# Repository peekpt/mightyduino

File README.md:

## Mightyduino
A DIY Arduino type hardware board based on ATmega644p Atmega1284p

This project is free and based on @MCUDude's [MightyCore](https://github.com/MCUdude/MightyCore) which has awesome well designed kits for serious development with AVR's.

Mightyduino is an Arduino with more memory than an Arduino Pro mini. It can use 644p (64k) or 1284p (128k) chips. Its voltage can be configured by U1 and the frequecy can be configured by the Murata's ressonator (crystal).
It has a power led and another one connected to pin D0. The push button performs reset. DTR pin can be used to external reset. The RAW pin is the input voltage **<16v**. The VCC pin is the regulator output and IC voltage, it can be loaded up to peak of **500mA**.

To burn the **bootloader** (optiboot 6.0) you must first install the [MightyCore boards](https://github.com/MCUdude/MightyCore#how-to-install) on Arduino App  , connect the ICSP pins to your bootloader programming hardware (eg. USBASP), select one of MCUDude's board that meet the specs you use and burn bootloader.
Then you can access (ttl-serial dongle) like a normal arduino on the serial pins (like arduino pro mini). Mightyduino uses the 'standard' pin mapping.

###Version History
- v1.3 - Changed C1 C3 footprint, add reset pin for SPI programming.
- v1.2 - Switch U1 shutdown pin 3 voltage to RAW
- v1.1 - Switched Led from pin D13 to D0, cosmetic improvements
- v1.0 - Initial release

###Quick Links:

Order boards from [OSHPark]
(https://oshpark.com/shared_projects/zuZ4OIae)

Or download the [Gerber files](https://github.com/peekpt/mightyduino/raw/master/gerber/gerbers.zip) for other pcb maker

Download the schematic [PDF](https://github.com/peekpt/mightyduino/blob/master/schematic.pdf)

ATmega datasheet [644p](http://www.atmel.com/images/doc2593.pdf) [1284p](http://www.atmel.com/images/doc8059.pdf)

## Screenshots

###Components

### Top

### Bottom

###Pin Mapping

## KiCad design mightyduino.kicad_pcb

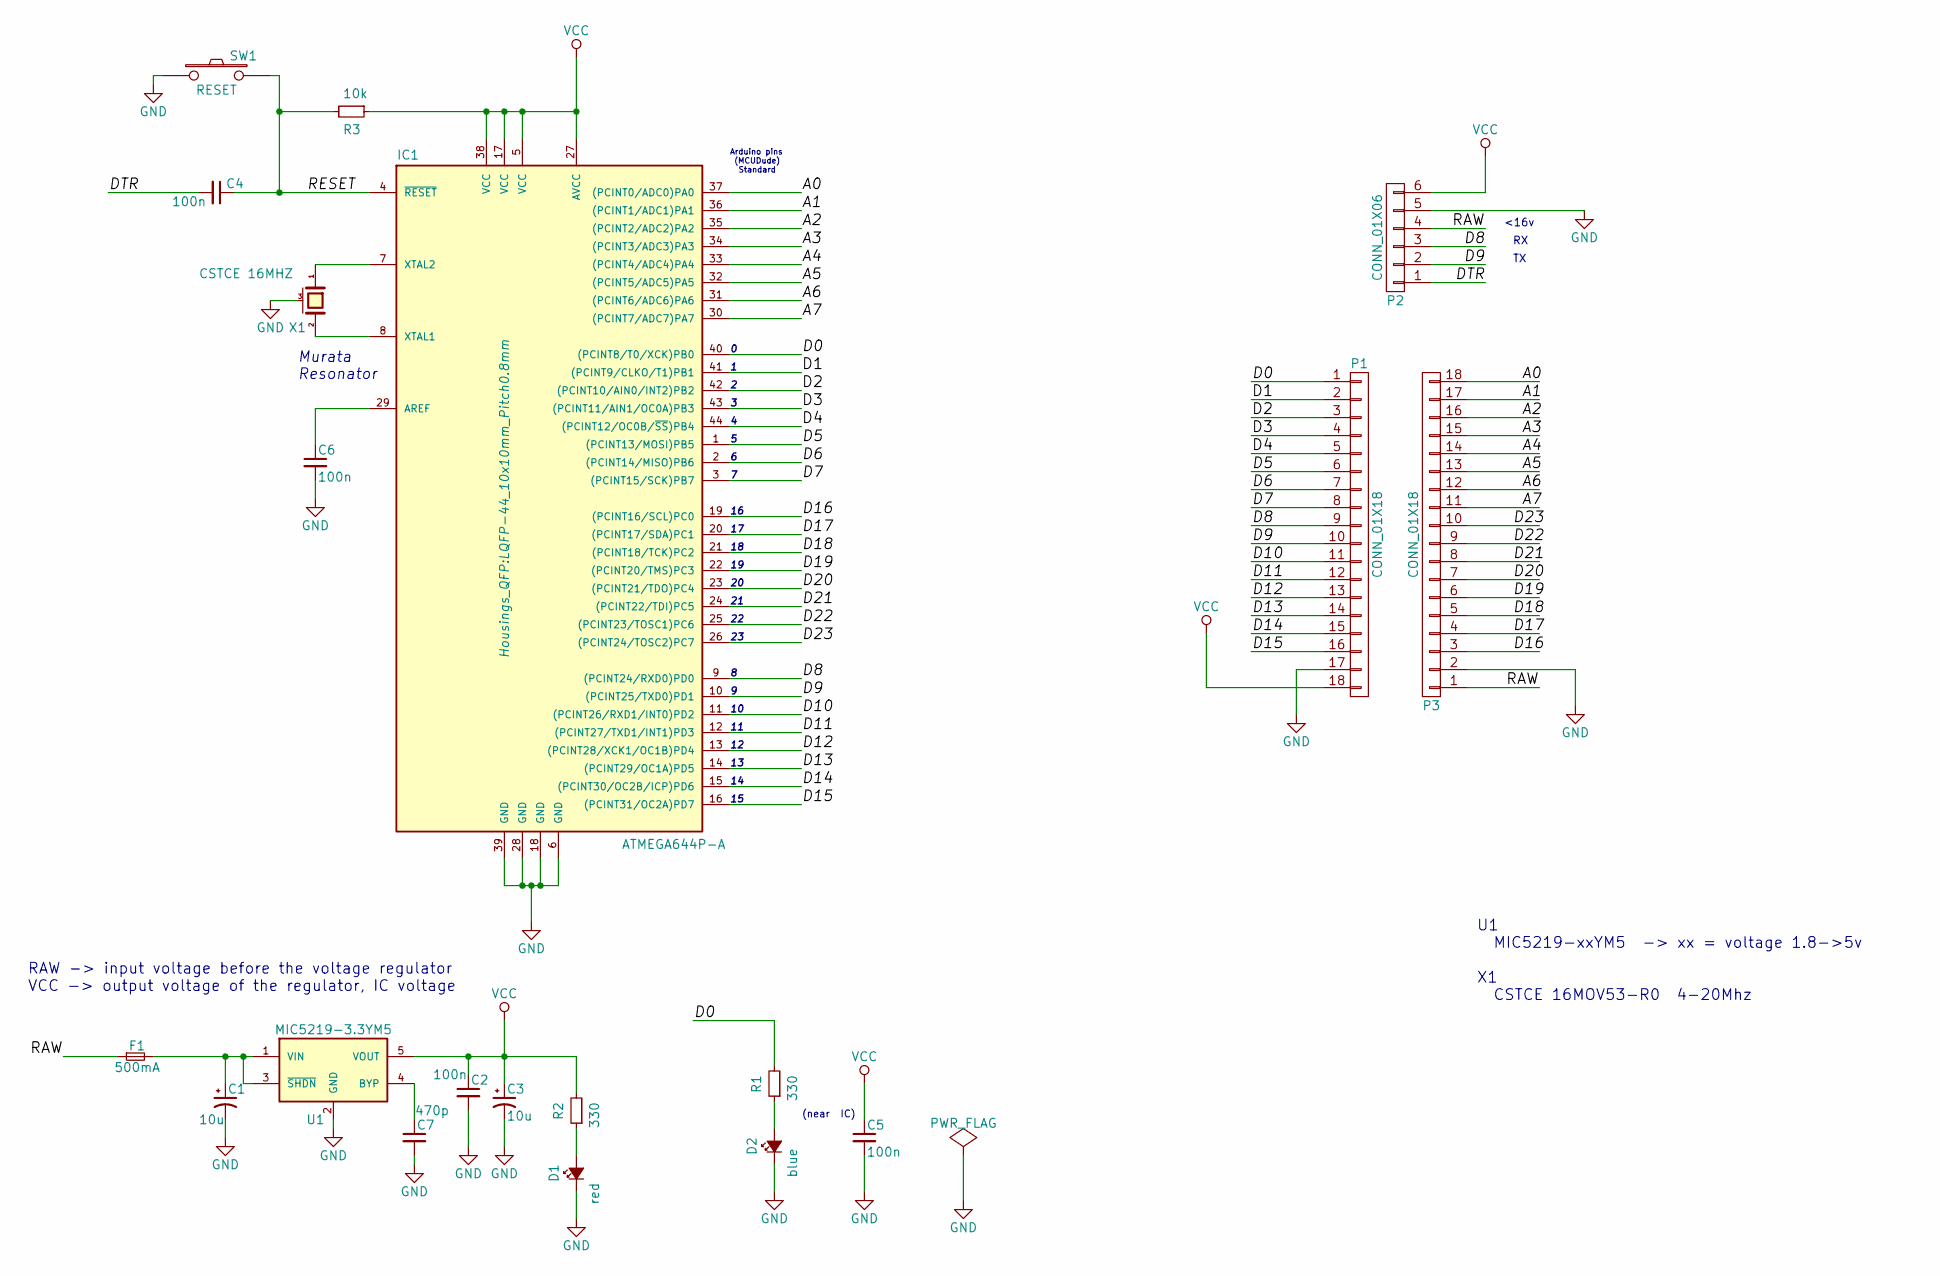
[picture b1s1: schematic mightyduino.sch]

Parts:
C1, C3: 10u; C_0805
C2, C4, C5, C6: 100n; C_0805
C7: 470p; C_0805
D1: red; LED_0805
D2: blue; LED_0805
F1: 500mA; C_0805_HandSoldering
IC1: ATMEGA644P-A; LQFP-44_10x10mm_Pitch0.8mm
P1, P3: CONN_01X18; Pin_Header_Straight_1x18
P2: CONN_01X06; Pin_Header_Straight_1x06
R1, R2: 330; R_0805
R3: 10k; R_0805
SW1: RESET; SW_SPST_TL3342
U1: MIC5219-3.3YM5; SOT-23-5
X1: CSTCE 16MHZ; CSTCEv2

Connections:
/A0: IC1.37 ((PCINT0/ADC0)PA0), P3.18
/A1: IC1.36 ((PCINT1/ADC1)PA1), P3.17
/A2: IC1.35 ((PCINT2/ADC2)PA2), P3.16
/A3: IC1.34 ((PCINT3/ADC3)PA3), P3.15
/A4: IC1.33 ((PCINT4/ADC4)PA4), P3.14
/A5: IC1.32 ((PCINT5/ADC5)PA5), P3.13
/A6: IC1.31 ((PCINT6/ADC6)PA6), P3.12
/A7: IC1.30 ((PCINT7/ADC7)PA7), P3.11
/D0: IC1.40 ((PCINT8/T0/XCK)PB0), P1.1, R1.2
/D1: IC1.41 ((PCINT9/CLKO/T1)PB1), P1.2
/D2: IC1.42 ((PCINT10/AIN0/INT2)PB2), P1.3
/D3: IC1.43 ((PCINT11/AIN1/OC0A)PB3), P1.4
/D4: IC1.44 ((PCINT12/OC0B/~SS~)PB4), P1.5
/D5: IC1.1 ((PCINT13/MOSI)PB5), P1.6
/D6: IC1.2 ((PCINT14/MISO)PB6), P1.7
/D7: IC1.3 ((PCINT15/SCK)PB7), P1.8
/D8: IC1.9 ((PCINT24/RXD0)PD0), P1.9, P2.3
/D9: IC1.10 ((PCINT25/TXD0)PD1), P1.10, P2.2
/D10: IC1.11 ((PCINT26/RXD1/INT0)PD2), P1.11
/D11: IC1.12 ((PCINT27/TXD1/INT1)PD3), P1.12
/D12: IC1.13 ((PCINT28/XCK1/OC1B)PD4), P1.13
/D13: IC1.14 ((PCINT29/OC1A)PD5), P1.14
/D14: IC1.15 ((PCINT30/OC2B/ICP)PD6), P1.15
/D15: IC1.16 ((PCINT31/OC2A)PD7), P1.16
/D16: IC1.19 ((PCINT16/SCL)PC0), P3.3
/D17: IC1.20 ((PCINT17/SDA)PC1), P3.4
/D18: IC1.21 ((PCINT18/TCK)PC2), P3.5
/D19: IC1.22 ((PCINT20/TMS)PC3), P3.6
/D20: IC1.23 ((PCINT21/TDO)PC4), P3.7
/D21: IC1.24 ((PCINT22/TDI)PC5), P3.8
/D22: IC1.25 ((PCINT23/TOSC1)PC6), P3.9
/D23: IC1.26 ((PCINT24/TOSC2)PC7), P3.10
/DTR: C4.2, P2.1
/RAW: F1.1, P2.4, P3.1
/RESET: C4.1, IC1.4 (~RESET), R3.2, SW1.2
GND: C1.2, C2.2, C3.2, C5.2, C6.2, C7.2, D1.1 (K), D2.1 (K), IC1.6 (GND), IC1.18 (GND), IC1.28 (GND), IC1.39 (GND), P1.17, P2.5, P3.2, SW1.1, U1.2 (GND), X1.3 (case)
unnamed: C1.1, F1.2, U1.1 (VIN), U1.3 (~SHDN~)
unnamed: C6.1, IC1.29 (AREF)
unnamed: C7.1, U1.4 (BYP)
unnamed: D1.2 (A), R2.1
unnamed: D2.2 (A), R1.1
unnamed: IC1.7 (XTAL2), X1.1
unnamed: IC1.8 (XTAL1), X1.2
VCC: C2.1, C3.1, C5.1, IC1.5 (VCC), IC1.17 (VCC), IC1.27 (AVCC), IC1.38 (VCC), P1.18, P2.6, R2.2, R3.1, U1.5 (VOUT)

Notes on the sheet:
Murata Resonator
Arduino pins (MCUDude) Standard
(near IC)
<16v
U1 MIC5219-xxYM5 -> xx = voltage 1.8->5v X1 CSTCE 16MOV53-R0 4-20Mhz
RAW -> input voltage before the voltage regulator VCC -> output voltage of the regulator, IC voltage

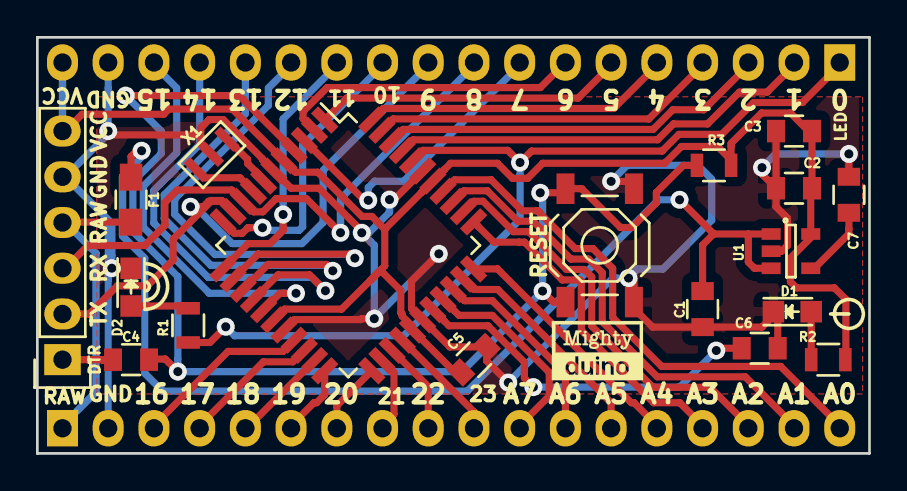
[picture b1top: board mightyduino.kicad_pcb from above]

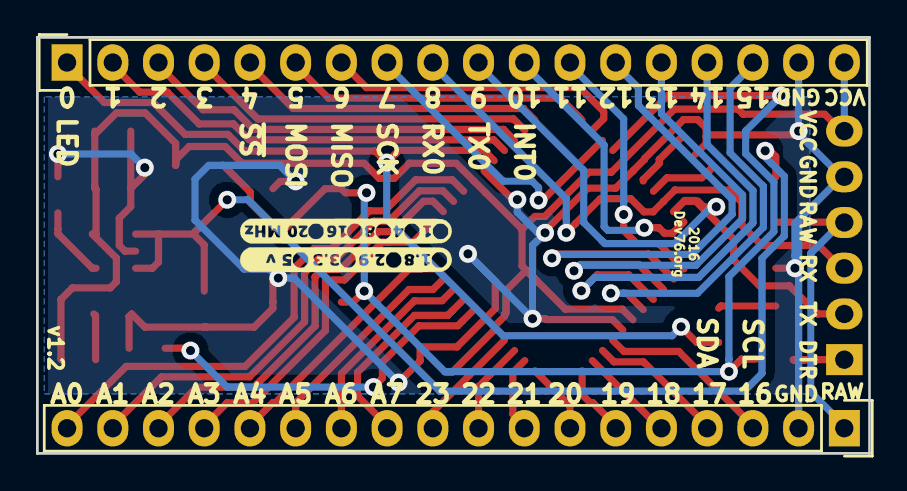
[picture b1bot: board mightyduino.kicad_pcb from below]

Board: 2 copper layers, 46.2 x 23.1 mm, 20 parts (2 on the bottom side), 44 nets.

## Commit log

2016-12-05 Public release 1.0
2016-12-05 add imgs
2016-12-05 .gitignore
2016-12-05 Update README.md
    readme is work in progress
2016-12-07 switched led from d13 to d0, cosmetic improvments
2016-12-07 readme update for version 1.1
2016-12-09 fix U1 pin 3 enable voltage
2016-12-09 release v1.2
2016-12-11 updated ressonator 3d design
2017-01-04 Removed front Silk logo (too small for printing)
2017-01-07 C1,C3 better footprint, added RESET PIN
2017-01-18 Added project footprintslibrary
